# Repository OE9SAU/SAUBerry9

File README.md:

# Based on the Radioberry projekt from pa3gsb i currently build up my own project called "SAUBerry9"

Whats inside?
- RadioBerry on a RPI4 with 7" touch
- [Power Latcher by OE9SAU](https://github.com/OE9SAU/SAUBerry9/tree/main/pwr_latcher)
- vswr temp bridge by OE9SAU (fork of the nice vswr master by pa3gsb) add the tempsensor to the board
- Radioberry_Console by VU2DLE
- ATU-100 (in progress)
- 50W or 100W PA (in progress)
- [SDR_PreAmp_Filter by OE9SAU](https://github.com/OE9SAU/SDR_PreAmp_Filter)
- LPF filterboard by ?? (in progress)
- Radioberry-Filters-Interface by cinosh07 (in progress)
- and some other stuff

-> Hope to get complete TRX-SDR running!

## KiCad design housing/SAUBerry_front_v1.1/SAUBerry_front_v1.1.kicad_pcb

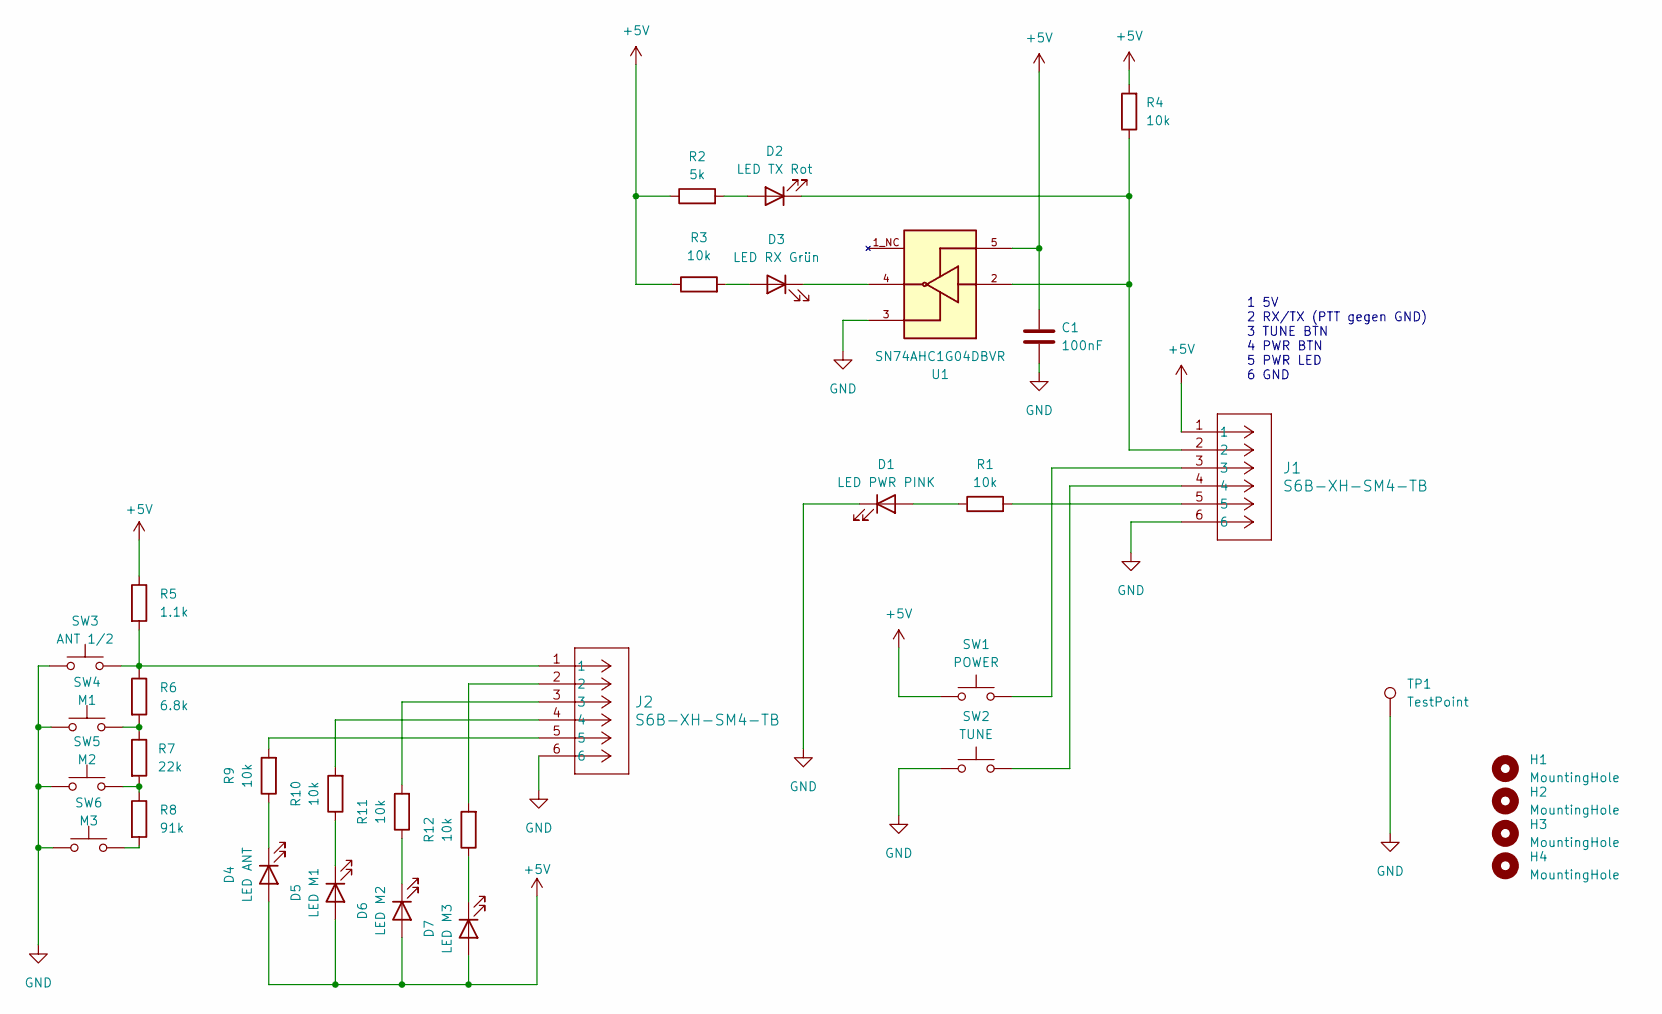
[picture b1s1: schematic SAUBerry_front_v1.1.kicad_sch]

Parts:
C1: 100nF; C_0805_2012Metric
D1: LED PWR PINK; LED_0805_2012Metric
D2: LED TX Rot; LED_0805_2012Metric
D3: LED RX Grün; LED_0805_2012Metric
D4: LED ANT; LED_0805_2012Metric
D5: LED M1; LED_0805_2012Metric
D6: LED M2; LED_0805_2012Metric
D7: LED M3; LED_0805_2012Metric
H1, H2, H3, H4: MountingHole; MountingHole_4.5mm
J1, J2: S6B-XH-SM4-TB; CONN_S6B-XH-SM4-TB_JST
R1, R3, R4, R9, R10, R11, R12: 10k; R_0805_2012Metric
R2: 5k; R_0805_2012Metric
R5: 1.1k; R_0805_2012Metric
R6: 6.8k; R_0805_2012Metric
R7: 22k; R_0805_2012Metric
R8: 91k; R_0805_2012Metric
SW1: POWER; SW_SPST_Omron_B3FS-101xP
SW2: TUNE; SW_SPST_Omron_B3FS-101xP
SW3: ANT 1/2; SW_SPST_Omron_B3FS-101xP
SW4: M1; SW_SPST_Omron_B3FS-101xP
SW5: M2; SW_SPST_Omron_B3FS-101xP
SW6: M3; SW_SPST_Omron_B3FS-101xP
TP1: TestPoint; TestPoint_Pad_4.0x4.0mm
U1: SN74AHC1G04DBVR; SOT95P280X145-5N; PARTREV AD

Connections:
+5V: C1.1, D4.2 (A), D5.2 (A), D6.2 (A), D7.2 (A), J1.1, R2.1, R3.1, R4.2, R5.1, SW1.1, U1.5
GND: C1.2, D1.1 (K), J1.6, J2.6, SW2.1, SW3.1, SW4.1, SW5.1, SW6.1, TP1.1, U1.3; also elsewhere on the board
unnamed: D1.2 (A), R1.1
unnamed: D2.2 (A), R2.2
unnamed: D2.1 (K), J1.2, R4.1, U1.2
unnamed: D3.2 (A), R3.2
unnamed: D3.1 (K), U1.4
unnamed: D4.1 (K), R9.1
unnamed: D5.1 (K), R10.1
unnamed: D6.1 (K), R11.1
unnamed: D7.1 (K), R12.1
unnamed: J1.3, SW1.2
unnamed: J1.4, SW2.2
unnamed: J1.5, R1.2
unnamed: J2.1, R5.2, R6.1, SW3.2
unnamed: J2.2, R12.2
unnamed: J2.3, R11.2
unnamed: J2.4, R10.2
unnamed: J2.5, R9.2
unnamed: R6.2, R7.1, SW4.2
unnamed: R7.2, R8.1, SW5.2
unnamed: R8.2, SW6.2

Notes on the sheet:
1 5V 2 RX/TX (PTT gegen GND) 3 TUNE BTN 4 PWR BTN 5 PWR LED 6 GND

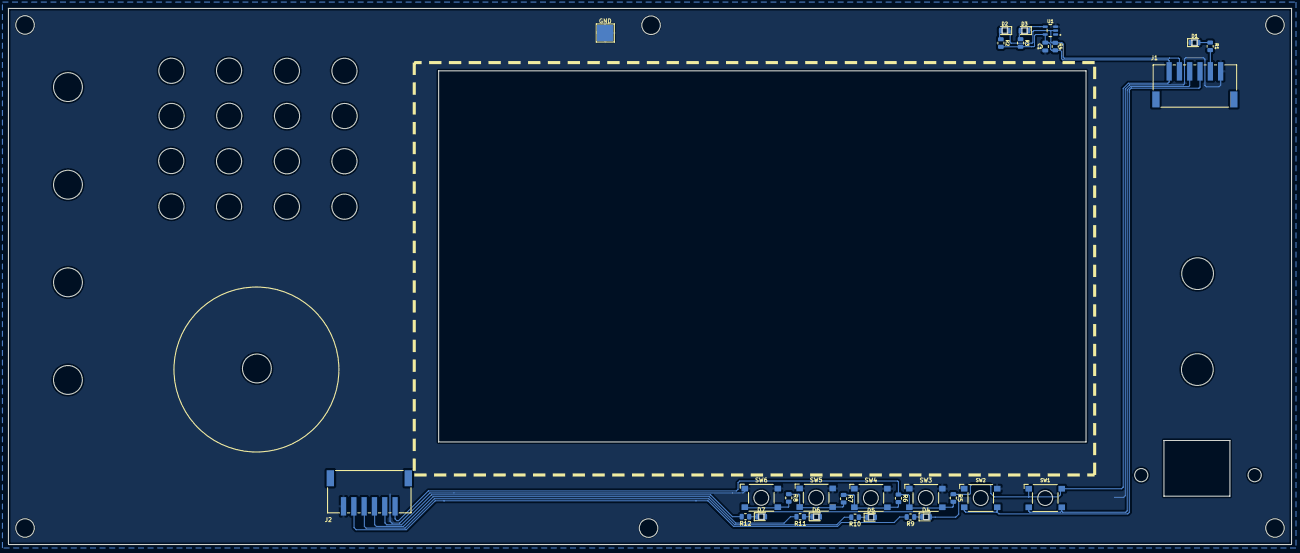
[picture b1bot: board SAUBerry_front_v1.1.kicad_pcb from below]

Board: 2 copper layers, 311.1 x 130.0 mm, 39 parts (30 on the bottom side), 22 nets.

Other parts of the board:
G0, G1, G4, G4#2, G101: LOGO
GND: TestPoint; TestPoint_Pad_4.0x4.0mm

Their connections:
GND: GND.1; also elsewhere on the board

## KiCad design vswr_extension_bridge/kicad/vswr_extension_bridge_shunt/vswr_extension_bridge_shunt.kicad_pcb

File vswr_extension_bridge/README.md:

# v2 fork by OE9SAU 
add the temp. sensor and current measurement from master preamp pcb to that small vswr bridge

VSWR - Module
==============================================

## Project:

For the radioberry this module gives the possibility for getting information about the vswr during transmit.

The module contains the possibility to measure the REF and FORWARD power.

Using a low speed i2c module makes it possible to read the data using the raspberry pi.

I have plans to add the reading:

-) to a seperate program to showing the measured data.
-) in the hpsdr emulator
-) in the pihpsdr plugin. 

Something about the setup.

The original design appeared in 1989 / 1990 SPRAT Magazine G-QRP
Also in the famous dutch QRP nieuwsbrief (NB 62) if found the article: "SWR METER ZONDER AFREGELING" door PAoWDW
I found it also in the openhpsdr ALEX project.

I did add the slow ADC i2c (as seen in the hermeslite version 2 design) 

## KICAD
Used KICAD to make the scheme and PCB.

Beside all this iam learning KICAD (stepped over from EAGLE). 
I like the KICAD program, much to learn, used start drawing a scheme. 
Add footprints and creating a PCB.

## Ordering
I ordered 6 January 2018 10 pcb at elecrow.

In the Netherlands it is possible to order at https://muxtronics.nl/ the components using the ShopCart from farnell.

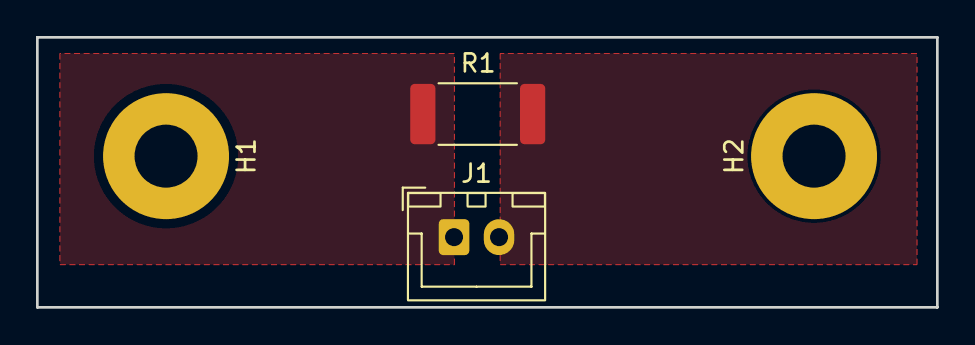
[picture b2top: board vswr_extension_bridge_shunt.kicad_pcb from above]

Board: 2 copper layers, 50.0 x 15.0 mm, 4 parts (0 on the bottom side), 2 nets, no tracks yet.

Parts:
H1, H2: MountingHole_Pad_MP; MountingHole_3.5mm_Pad
J1: Conn_01x02_Pin; JST_XH_B2B-XH-A_1x02_P2.50mm_Vertical
R1: R002; R_2512_6332Metric_Pad1.40x3.35mm_HandSolder

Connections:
unnamed: J1.1, R1.2
unnamed: J1.2, R1.1

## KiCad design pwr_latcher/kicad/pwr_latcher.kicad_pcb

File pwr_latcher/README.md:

# Power-Latcher für Raspberry Pi 4 / Radioberry

Der Taster löst einen sauberen Shutdown aus. Danach signalisiert GPIO15 der Un-Latch-Schaltung, die Versorgung verzögert abzuschalten. Ein eigenes Shutdown-Skript ist nicht erforderlich.

**Ablauf:** Taster loslassen → sauberer Shutdown → GPIO15 HIGH → RC-Verzögerung → Versorgung aus.

## Anschlüsse

| Funktion | BCM / GPIO | Physischer Pin |
|---|---|---|
| Shutdown-Taster gegen GND | GPIO14 | 8 |
| Un-Latch, aktiv HIGH | GPIO15 | 10 |
| Masse | GND | z. B. 9 |

GPIO14/15 dürfen nicht gleichzeitig vom UART oder der seriellen Konsole verwendet werden. Falls nötig unter `sudo raspi-config` → **Interface Options → Serial Port** beide deaktivieren. GPIO-Pegel: **3,3 V**.

## Raspberry-Pi-Einstellungen

```bash
sudo nano /boot/firmware/config.txt
```

Am Ende ergänzen; vorhandene gleiche Overlay-Einträge anpassen statt doppelt eintragen:

```ini
[all]

# Taster → Shutdown (GPIO14, Pin 8, gegen GND)
dtoverlay=gpio-shutdown,gpio_pin=14,active_low=1,gpio_pull=up

# GPIO15 / Pin 10 beim Booten als Ausgang auf LOW
gpio=15=op,dl

# Poweroff-Signal → Un-Latch (GPIO15, Pin 10, aktiv HIGH)
dtoverlay=gpio-poweroff,gpiopin=15
```

Beim Poweroff-Overlay **kein `active_low=1`** ergänzen. GPIO15 bleibt nach der Initialisierung LOW und wird am Ende des Shutdowns HIGH. Der Pegel unmittelbar nach dem Einschalten muss bei Bedarf durch die Hardware abgesichert sein.

Speichern und neu starten:

```bash
sudo reboot
```

## labwc: direkt herunterfahren, ohne Menü

Als Benutzer des Pi-Desktops ausführen:

```bash
mkdir -p ~/.config/labwc
[ -f ~/.config/labwc/rc.xml ] || cp /etc/xdg/labwc/rc.xml ~/.config/labwc/rc.xml
cp ~/.config/labwc/rc.xml ~/.config/labwc/rc.xml.bak
nano ~/.config/labwc/rc.xml
```

Direkt **vor `</keyboard>`** einfügen. Einen vorhandenen `XF86PowerOff`-Eintrag ersetzen:

```xml
<keybind key="XF86PowerOff" onRelease="yes">
  <action name="Execute">
    <command>systemctl poweroff</command>
  </action>
</keybind>
```

Andere Einstellungen erhalten; XML darf auch in einer Zeile stehen. Speichern mit **Strg+O**, Enter, **Strg+X**.

Konfiguration neu laden, auch über SSH als Desktop-Benutzer:

```bash
pkill -HUP -x labwc
```

Der Taster löst nun beim Loslassen direkt den Shutdown aus.

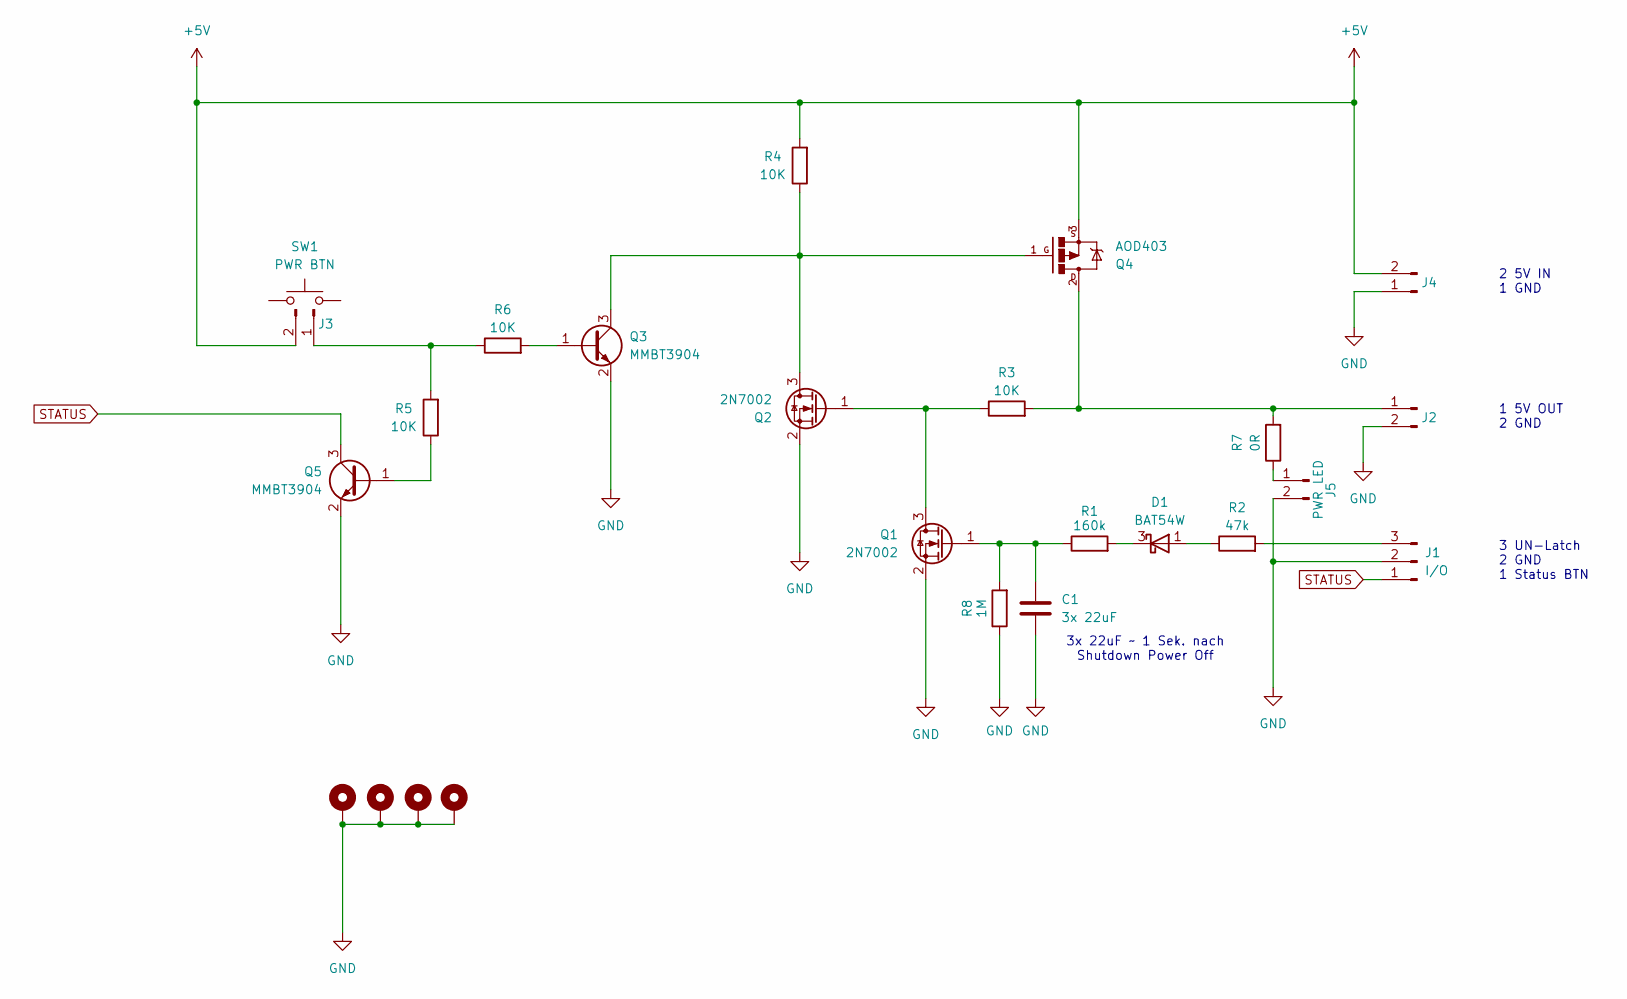
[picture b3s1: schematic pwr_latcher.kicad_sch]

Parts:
C1: 3x 22uF; C_0805_2012Metric
D1: BAT54W; SOT-323_SC-70
H1, H2, H3, H4: MountingHole_Pad; MountingHole_3.5mm_Pad
J1: I/O; PinHeader_1x03_P2.54mm_Vertical
J2, J4: 5V OUT; JST_XH_B2B-XH-A_1x02_P2.50mm_Vertical
J3: Conn_01x02_Pin; PinHeader_1x02_P2.54mm_Vertical
J5: PWR LED; PinHeader_1x02_P2.54mm_Vertical
Q1, Q2: 2N7002; SOT-23
Q3, Q5: MMBT3904; SOT-23
Q4: AOD403; TO252
R1: 160k; R_0805_2012Metric
R2: 47k; R_0805_2012Metric
R3, R4, R5, R6: 10K; R_0805_2012Metric
R7: 0R; R_0805_2012Metric
R8: 1M; R_0805_2012Metric
SW1: PWR BTN

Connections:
+5V: J3.2, J4.2, Q4.3, R4.2
GND: C1.2, H1.1, H2.1, H3.1, H4.1, J1.2, J2.2, J4.1, J5.2, Q1.2 (S), Q2.2 (S), Q3.2 (E), Q5.2 (E), R8.1
unnamed: D1.1 (A), R2.1
unnamed: D1.3 (K), R1.2
unnamed: J1.3, R2.2
unnamed: J2.1, Q4.2, R3.2, R7.2
unnamed: J3.1, R5.2, R6.1
unnamed: J5.1, R7.1
unnamed: Q1.3 (D), Q2.1 (G), R3.1
unnamed: C1.1, Q1.1 (G), R1.1, R8.2
unnamed: Q2.3 (D), Q3.3 (C), Q4.1, R4.1
unnamed: Q3.1 (B), R6.2
unnamed: Q5.1 (B), R5.1
STATUS: J1.1, Q5.3 (C)

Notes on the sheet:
2 5V IN 1 GND
1 5V OUT 2 GND
3x 22uF ~ 1 Sek. nach Shutdown Power Off
3 UN-Latch 2 GND 1 Status BTN

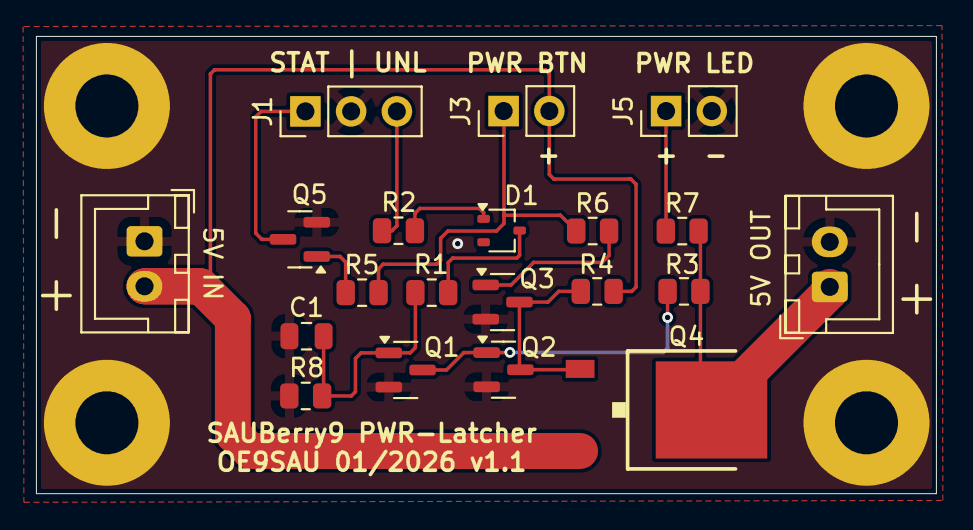
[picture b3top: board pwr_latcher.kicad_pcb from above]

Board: 2 copper layers, 50.0 x 25.4 mm, 25 parts (1 on the bottom side), 14 nets.

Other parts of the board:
g1: LOGO

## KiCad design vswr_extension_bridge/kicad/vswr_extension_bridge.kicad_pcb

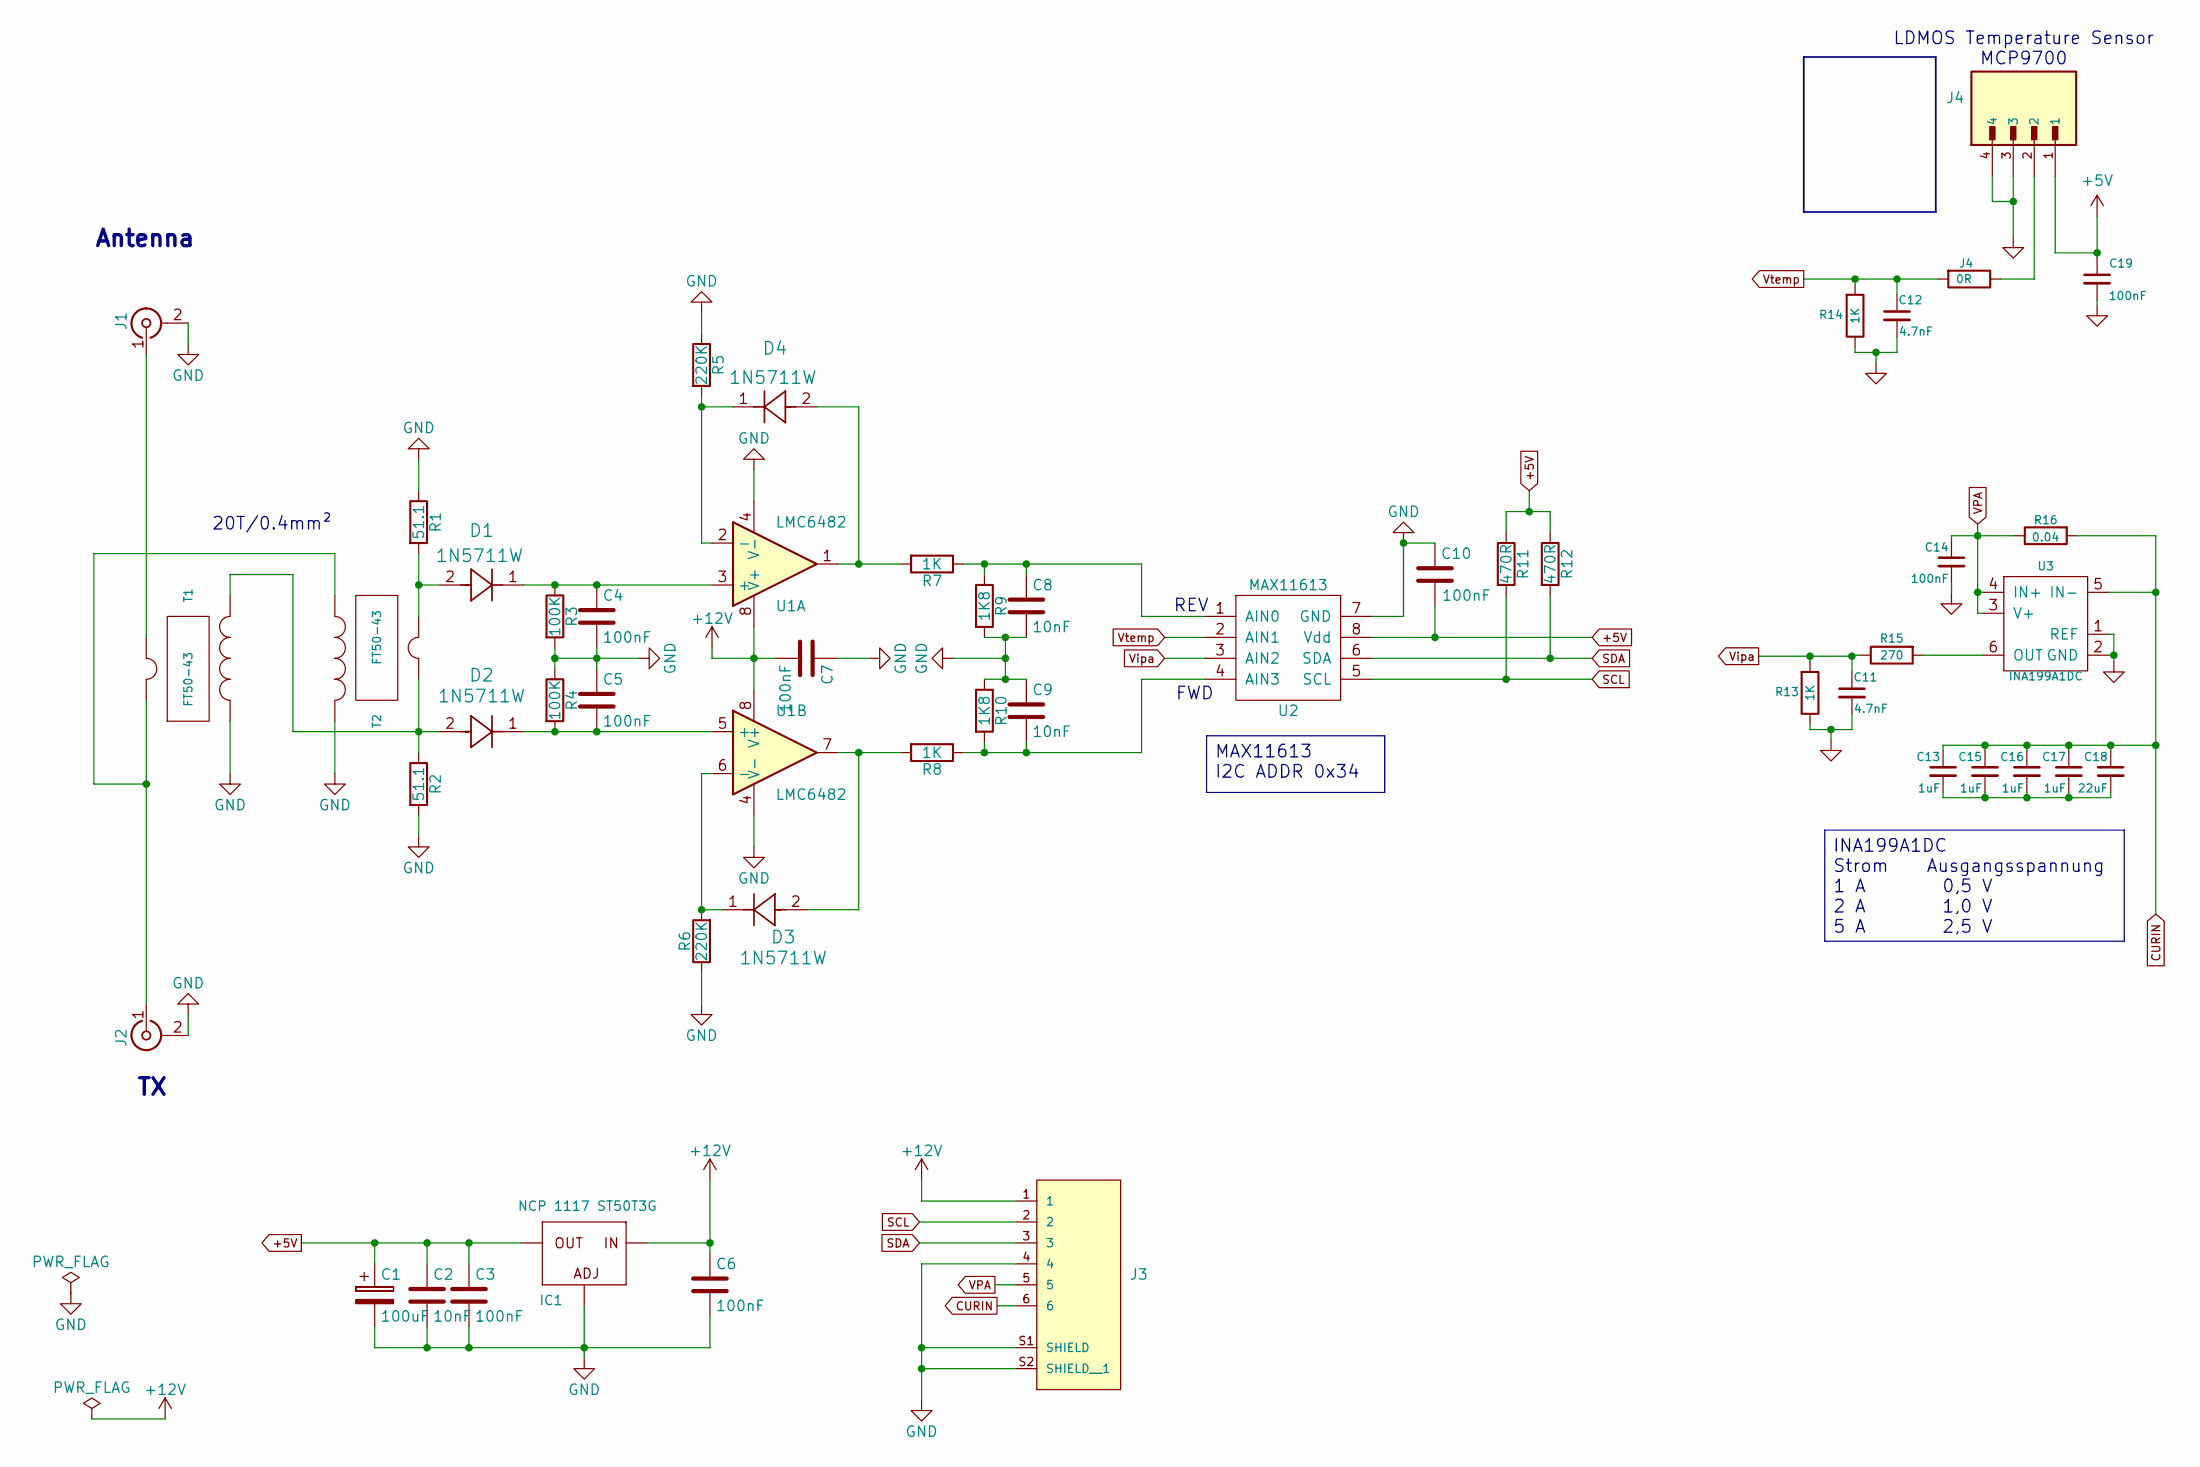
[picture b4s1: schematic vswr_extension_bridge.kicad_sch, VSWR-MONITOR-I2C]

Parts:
C1: 100uF; SMD-1210
C2, C8, C9: 10nF; C_0805_2012Metric
C3, C4, C5, C6, C7, C14, C19: 100nF; C_0805_2012Metric
C10: 100nF; C_0805_HandSoldering
C11, C12: 4.7nF; C_0805_2012Metric
C13, C15, C16, C17: 1uF; SMD-0805
C18: 22uF; SMD-0805
D1, D2, D3, D4: 1N5711W; SOD123_DIO
IC1: NCP 1117 ST50T3G; V-REG_SOT223
J1, J2: DNI; SMAVERT
J3: S6B-PH-SM4-TB_LF__SN_; JST_S6B-PH-SM4-TB_LF__SN_
J4: 0R; R_0805_2012Metric
R1, R2: 51.1; D_2010_5025Metric
R3, R4: 100K; R_0805_2012Metric
R5, R6: 220K; R_0805_2012Metric
R7, R8, R13, R14: 1K; R_0805_2012Metric
R9, R10: 1K8; R_0805_2012Metric
R11, R12: 470R; R_0805_2012Metric
R15: 270; R_0805_2012Metric
R16: 0.04; R_1206_3216Metric
T1, T2: FT50-43; T50-43_V_THT
U1: LMC6482; SOIC-8_3.9x4.9mm_Pitch1.27mm
U2: MAX11613
U3: INA199A1DC; PE4259

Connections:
+12V: C6.1, C7.2, IC1.3 (IN), J3.1, U1.8 (V+)
CURIN: C13.1, C15.1, C16.1, C17.1, C18.1, J3.6, R16.2, U3.5 (IN-)
GND: C1.2, C2.2, C3.2, C4.2, C5.1, C6.2, C7.1, C8.2, C9.1, C10.1, C11.2, C12.2, C14.2, C19.2, IC1.1 (ADJ), J1.2 (Ext), J2.2 (Ext), J3.4, J3.S1 (SHIELD), J3.S2 (SHIELD__1), J4.3, J4.4, R1.1, R2.2, R3.2, R4.1, R5.1, R6.1, R9.2, R10.1, R13.1, R14.1, T1.3 (sec1), T2.4 (sec2), U1.4 (V-), U2.7 (GND), U3.1 (REF), U3.2 (GND)
unnamed: C13.2, C15.2, C16.2, C17.2, C18.2
unnamed: D3.2, R8.2, U1.7
unnamed: D4.2, R7.2, U1.1
unnamed: J1.1 (In), T1.2 (pri2)
unnamed: J2.1 (In), T1.1 (pri), T2.3 (sec1)
unnamed 8: J4.2; also elsewhere on the board
unnamed: D2.2, R2.1, T1.4 (sec2), T2.2 (pri2)
unnamed: D1.2, R1.2, T2.1 (pri)
unnamed: C4.1, D1.1, R3.1, U1.3 (+)
unnamed: D4.1, R5.2, U1.2 (-)
unnamed: C5.2, D2.1, R4.2, U1.5 (+)
unnamed: D3.1, R6.2, U1.6 (-)
unnamed: C8.1, R7.1, R9.1, U2.1 (AIN0)
unnamed: C9.2, R8.1, R10.2, U2.4 (AIN3)
unnamed: R15.2, U3.6 (OUT)
SCL: J3.2, R11.2, U2.5 (SCL)
SDA: J3.3, R12.2, U2.6 (SDA)
VPA: C14.1, J3.5, R16.1, U3.3 (V+), U3.4 (IN+)
Vipa: C11.1, R13.2, R15.1, U2.3 (AIN2)

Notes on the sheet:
LDMOS Temperature Sensor MCP9700
FWD
Antenna
REV
20T/0.4mm²
MAX11613 I2C ADDR 0x34
INA199A1DC Strom Ausgangsspannung 1 A 0,5 V 2 A 1,0 V 5 A 2,5 V

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
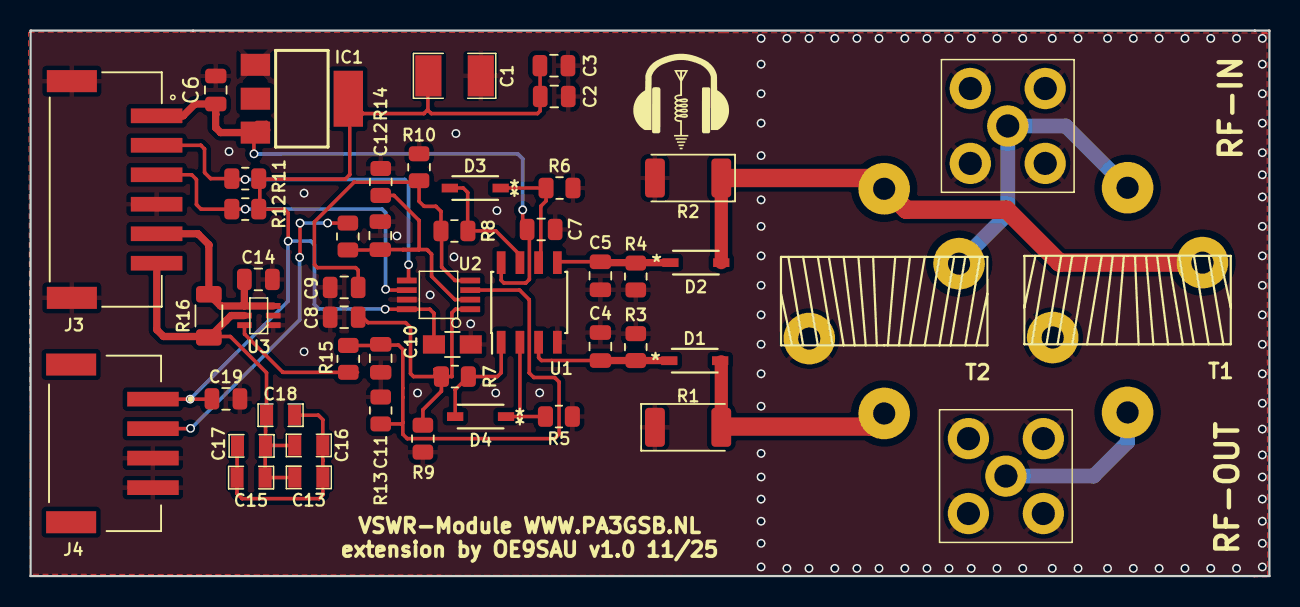
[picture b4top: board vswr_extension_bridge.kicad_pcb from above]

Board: 2 copper layers, 84.0 x 37.0 mm, 51 parts (0 on the bottom side), 24 nets.

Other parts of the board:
G10: LOGO
J4#2: 0R; R_0805_2012Metric

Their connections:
unnamed 8: J4#2.2; also elsewhere on the board

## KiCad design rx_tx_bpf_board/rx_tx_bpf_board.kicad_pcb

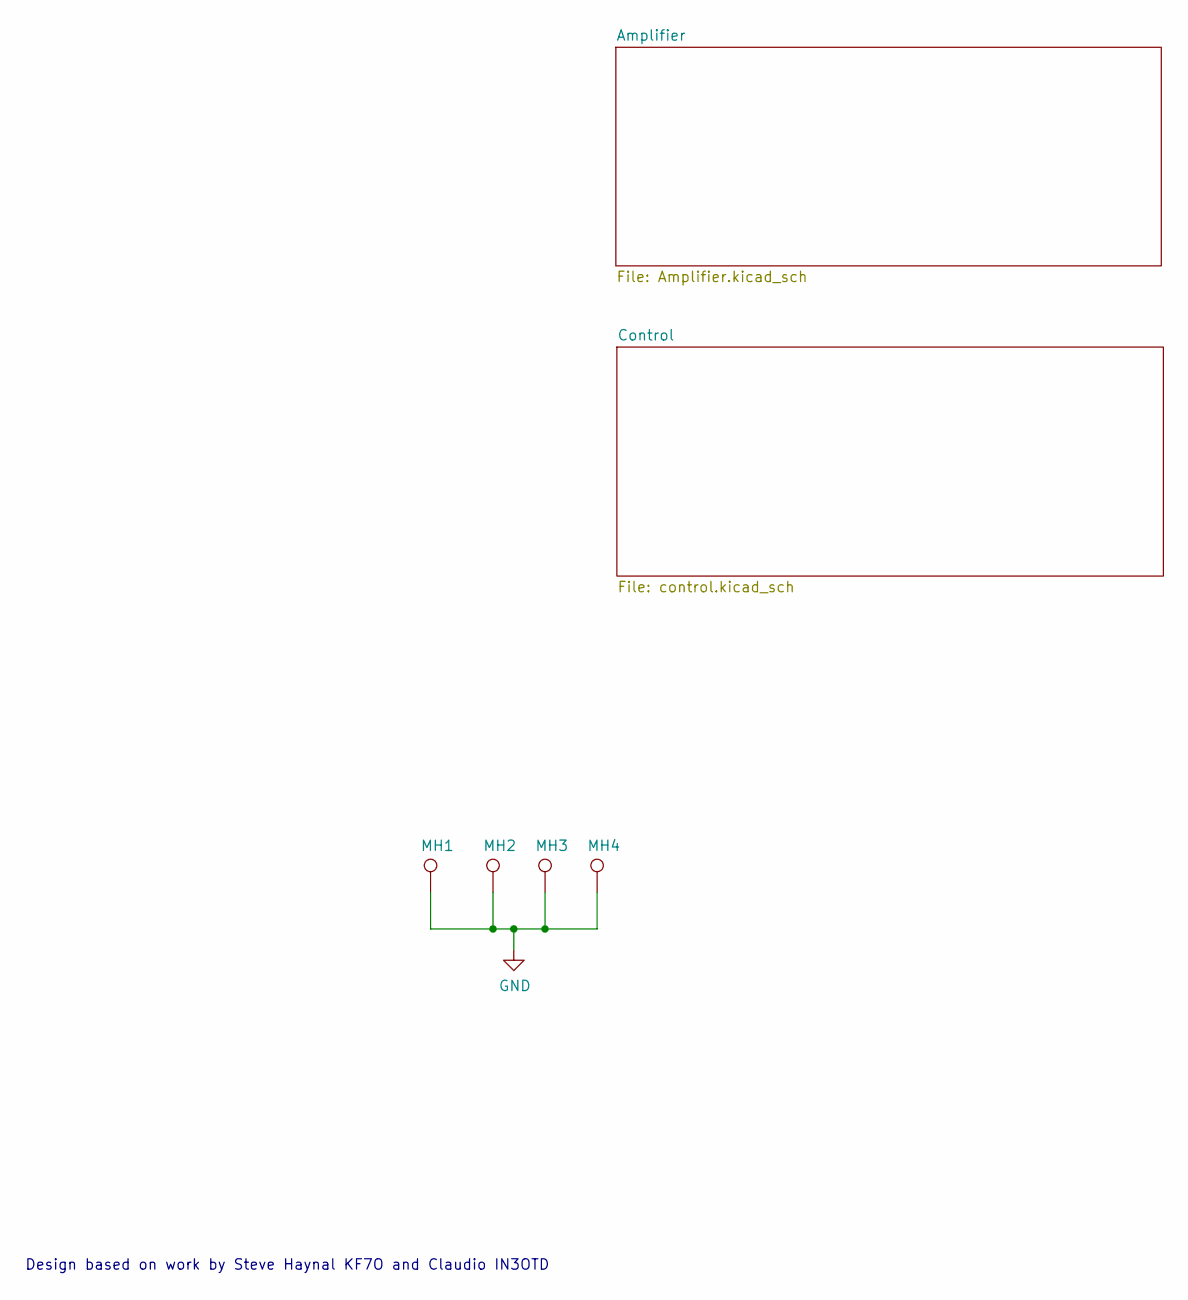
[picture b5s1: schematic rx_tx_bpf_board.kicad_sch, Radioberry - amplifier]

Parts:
MH1, MH2, MH3, MH4: DNI; m3

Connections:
GND: MH1.1, MH2.1, MH3.1, MH4.1; also elsewhere on the board

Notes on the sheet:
Design based on work by Steve Haynal KF7O and Claudio IN3OTD

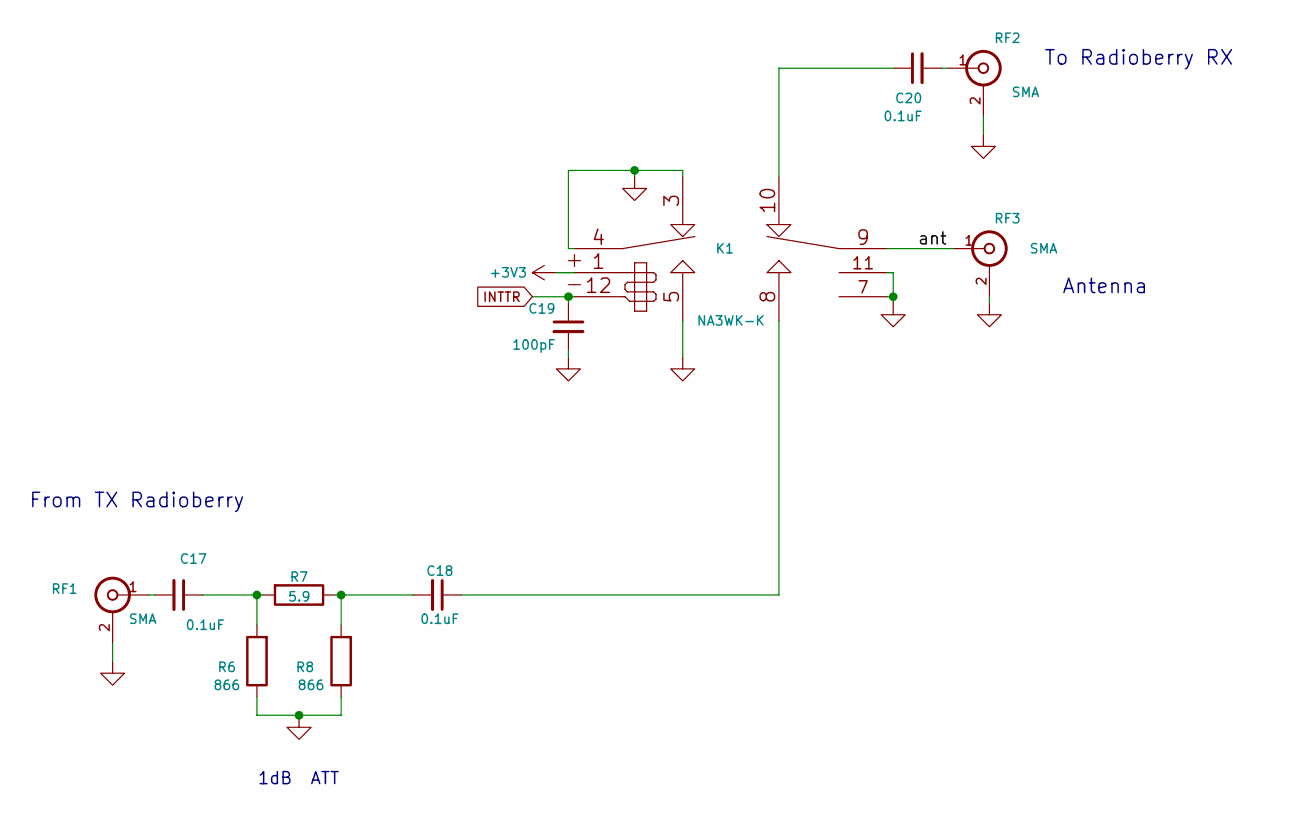
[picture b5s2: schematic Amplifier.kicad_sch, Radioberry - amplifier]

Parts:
C17, C18, C20: 0.1uF; SMD-0603
C19: 100pF; SMD-0805
K1: NA3WK-K; DPDT_GND
R6, R8: 866; SMD-0805
R7: 5.9; SMD-0805
RF1, RF2, RF3: SMA; SMAEDGE_THFULL_L

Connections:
+3V3: K1.1; also elsewhere on the board
/Amplifier/ant: K1.9, RF3.1 (In)
GND: C19.2, K1.3, K1.4, K1.5, K1.7, K1.11, R6.1, R8.1, RF1.2 (Ext), RF2.2 (Ext), RF3.2 (Ext); also elsewhere on the board
INTTR: C19.1, K1.12; also elsewhere on the board
unnamed: C17.1, R6.2, R7.2
unnamed: C18.1, K1.8
unnamed: C18.2, R7.1, R8.2
unnamed: C20.1, K1.10
unnamed: C17.2, RF1.1 (In)
unnamed: C20.2, RF2.1 (In)

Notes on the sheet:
1dB ATT
To Radioberry RX
From TX Radioberry
Antenna

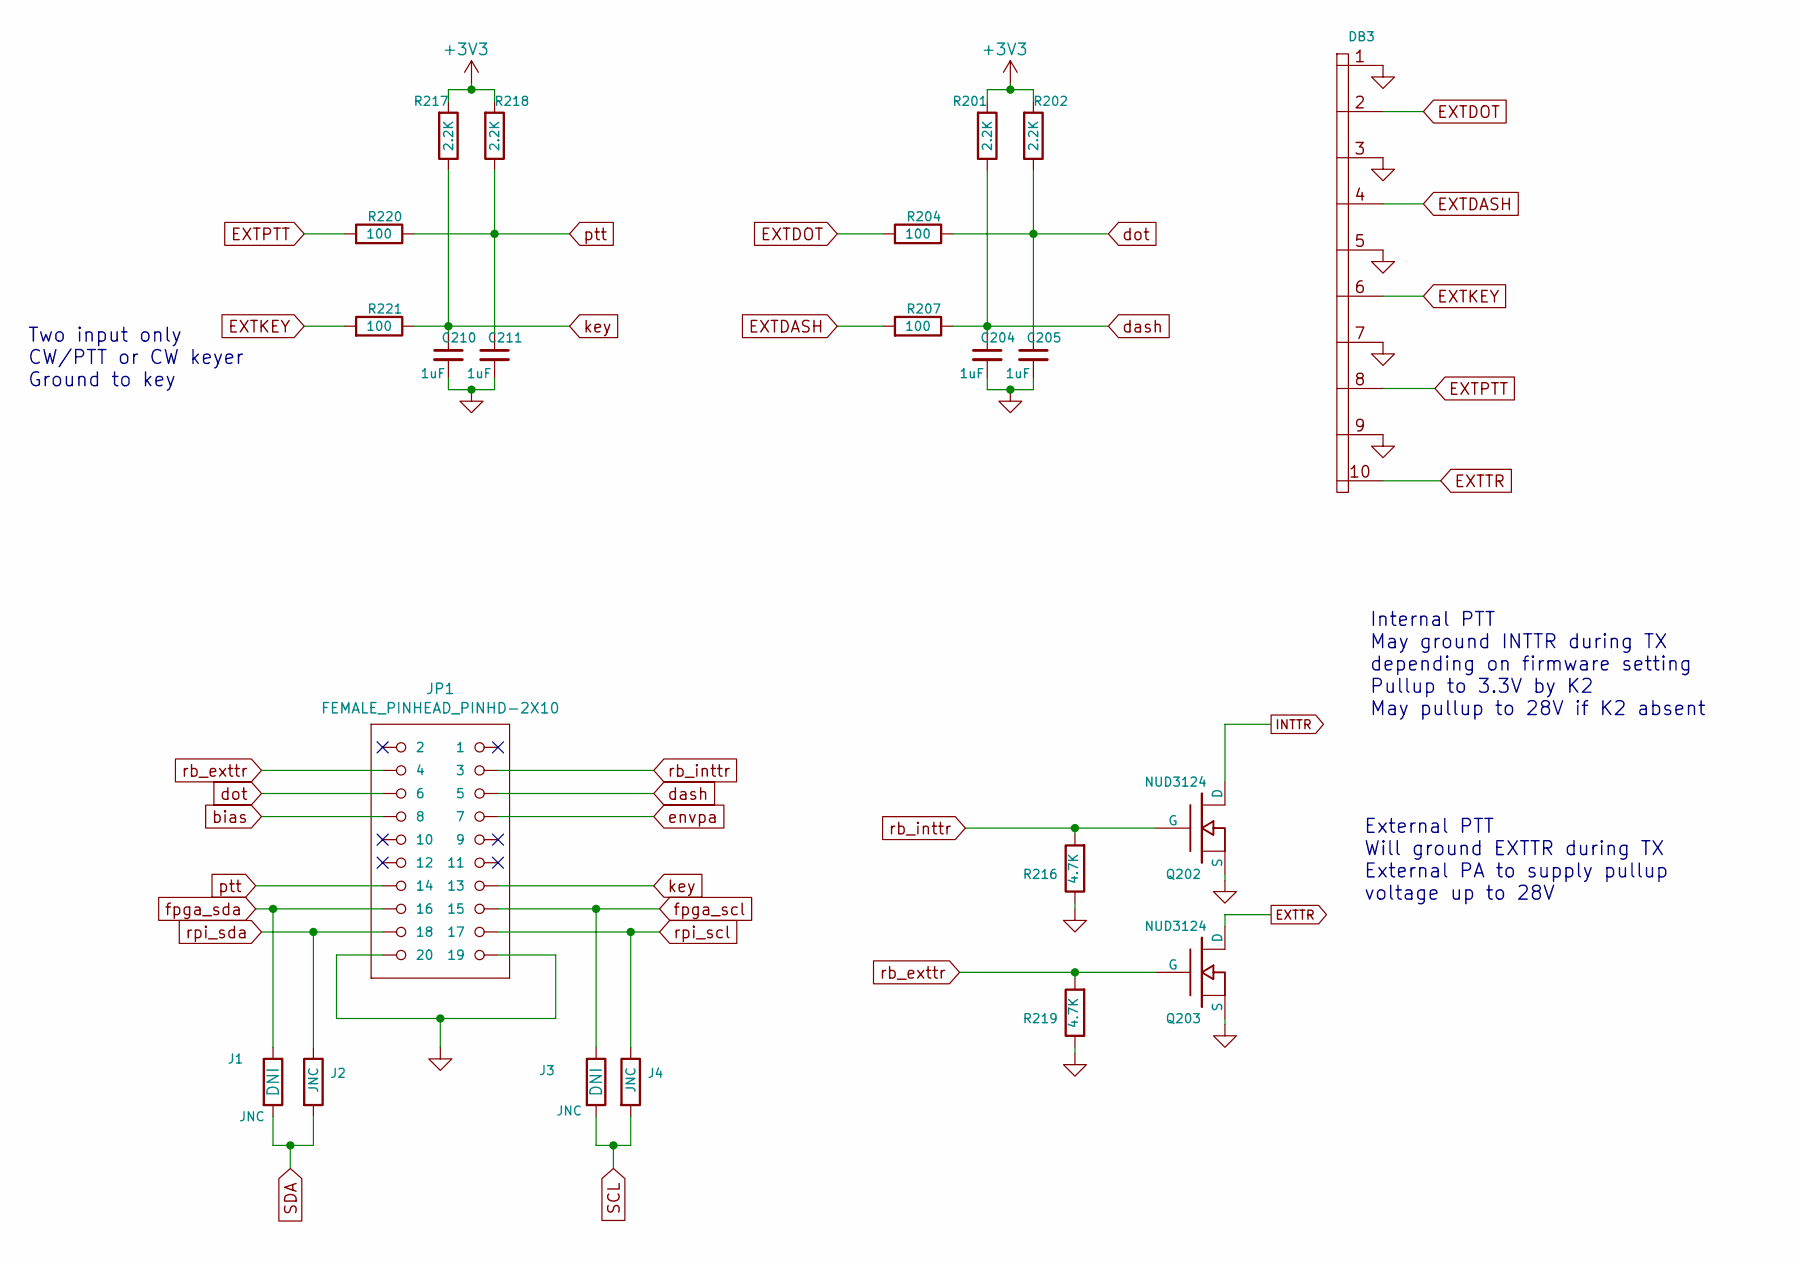
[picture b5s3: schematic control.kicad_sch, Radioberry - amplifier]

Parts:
C204, C205, C210, C211: 1uF; SMD-0603
DB3: IO10; 5x2
J1, J2, J3, J4: JNC; SMD-0603
JP1: FEMALE_PINHEAD_PINHD-2X10; PINHEAD_2X10
Q202, Q203: NUD3124; SOT23_3
R201, R202, R217, R218: 2.2K; SMD-0603
R204, R207, R220, R221: 100; SMD-0603
R216, R219: 4.7K; SMD-0603

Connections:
+3V3: R201.2, R202.2, R217.2, R218.2; also elsewhere on the board
EXTDASH: DB3.4, R207.2
EXTDOT: DB3.2, R204.2
EXTKEY: DB3.6, R221.2
EXTPTT: DB3.8, R220.2
EXTTR: DB3.10, Q203.3 (D)
GND: C204.2, C205.2, C210.2, C211.2, DB3.1, DB3.3, DB3.5, DB3.7, DB3.9, JP1.19, JP1.20, Q202.2 (S), Q203.2 (S), R216.1, R219.1; also elsewhere on the board
INTTR: Q202.3 (D); also elsewhere on the board
SCL: J3.1, J4.1
SDA: J1.1, J2.1
bias: JP1.8
dash: C204.1, JP1.5, R201.1, R207.1
dot: C205.1, JP1.6, R202.1, R204.1
envpa: JP1.7
fpga_scl: J3.2, JP1.15
fpga_sda: J1.2, JP1.16
key: C210.1, JP1.13, R217.1, R221.1
ptt: C211.1, JP1.14, R218.1, R220.1
rb_exttr: JP1.4, Q203.1 (G), R219.2
rb_inttr: JP1.3, Q202.1 (G), R216.2
rpi_scl: J4.2, JP1.17
rpi_sda: J2.2, JP1.18

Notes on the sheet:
External PTT Will ground EXTTR during TX External PA to supply pullup voltage up to 28V
Two input only CW/PTT or CW keyer Ground to key
Internal PTT May ground INTTR during TX depending on firmware setting Pullup to 3.3V by K2 May pullup to 28V if K2 absent

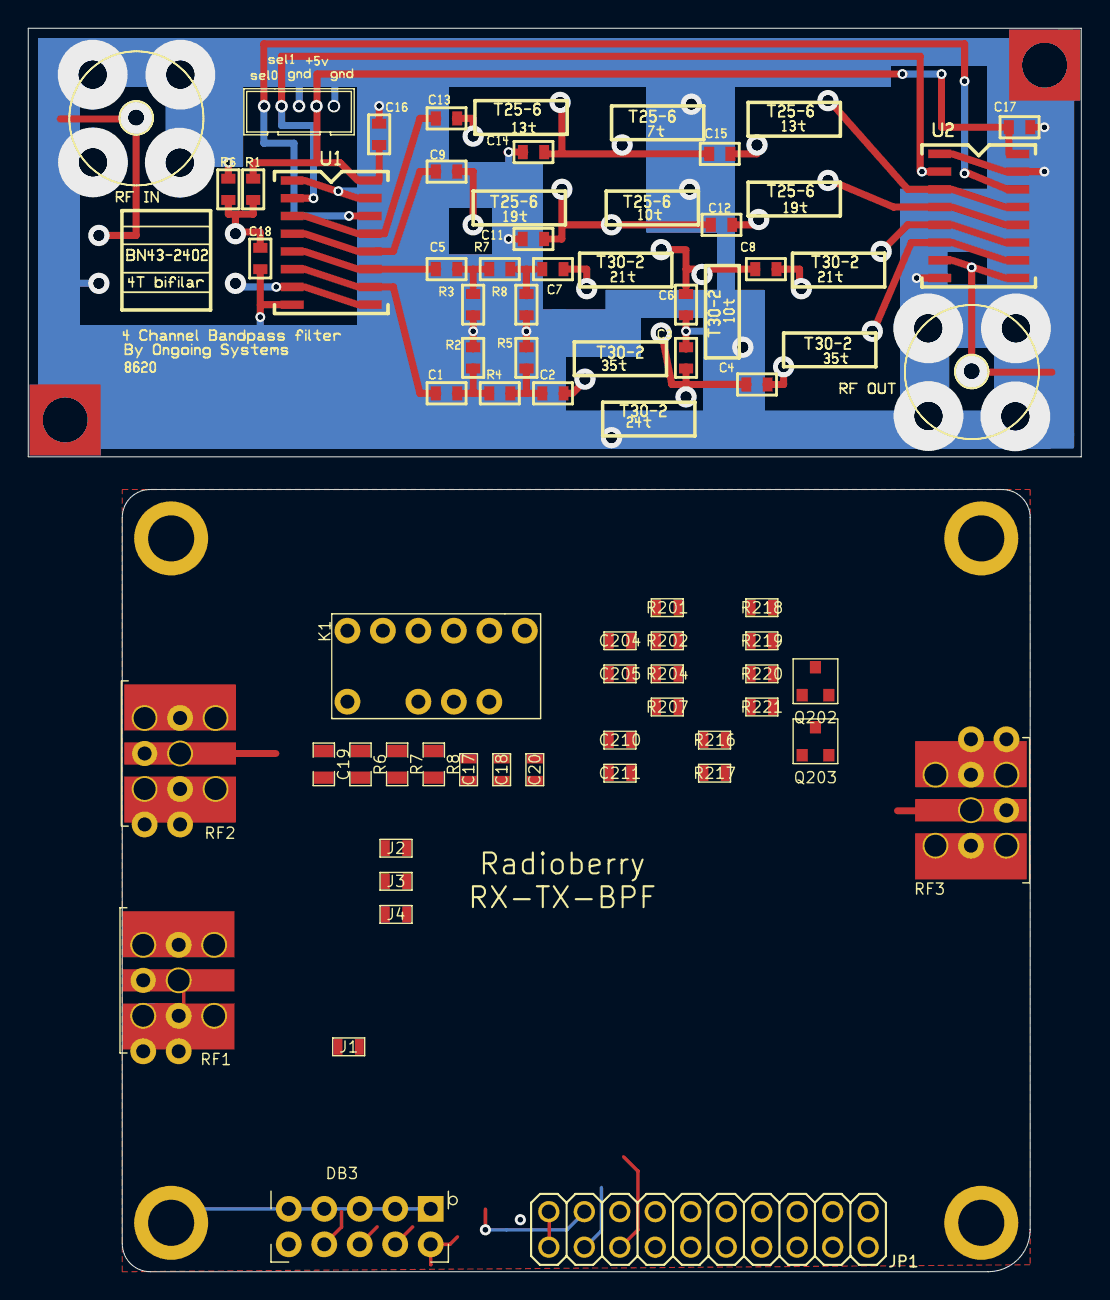
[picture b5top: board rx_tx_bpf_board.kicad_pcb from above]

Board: 2 copper layers, 75.4 x 89.0 mm, 37 parts (0 on the bottom side), 27 nets.

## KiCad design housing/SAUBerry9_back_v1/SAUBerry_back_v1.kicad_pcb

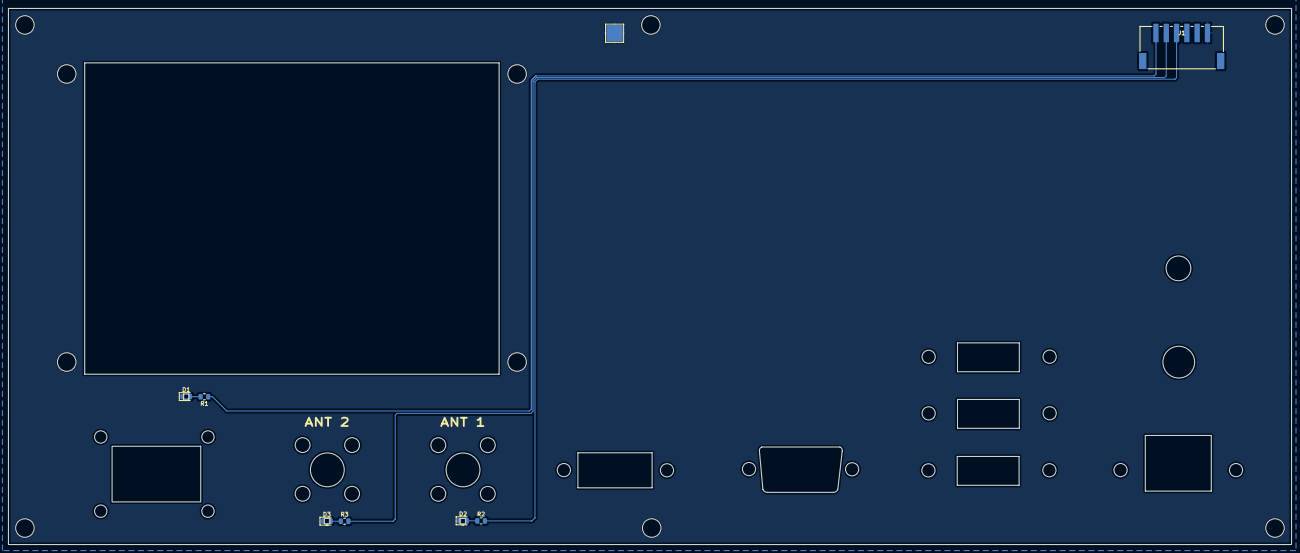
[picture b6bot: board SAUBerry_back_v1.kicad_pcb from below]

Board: 2 copper layers, 311.1 x 130.0 mm, 29 parts (10 on the bottom side), 7 nets.

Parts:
D1, D2, D3: LED; LED_0805_2012Metric
G1, G2, G4, G10, G21, G21#2, G21#3, G30, G105: LOGO
GND: TestPoint; TestPoint_Pad_4.0x4.0mm
H1, H1#2, H1#3, H1#4, H1#5, H1#6, H1#7, H2, H3, H4: MountingHole; MountingHole_4.5mm
J1: S6B-XH-SM4-TB; CONN_S6B-XH-SM4-TB_JST
R1, R2, R3: 10k; R_0805_2012Metric
ant1, ant2: N-Buchse_SMA_IN_LED

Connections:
GND: D1.1 (K), D2.1 (K), D3.1 (K), GND.1, J1.6
unnamed: D1.2 (A), R1.2
unnamed: D2.2 (A), R2.2
unnamed: D3.2 (A), R3.1
unnamed: J1.1, R1.1
unnamed: J1.2, R3.2
unnamed: J1.3, R2.1
